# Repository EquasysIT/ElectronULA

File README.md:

# ElectronULA
Project to create replacement ULA board for the Acorn Electron. See Wiki

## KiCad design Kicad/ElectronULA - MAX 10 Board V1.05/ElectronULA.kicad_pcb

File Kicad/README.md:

The Core Carrier board is a board which requires the "EEpizza" board to be fitted. This is a board which actually contains the FPGA.
The MAX 10 Board is a complete board with everything required to replace the Acorn Electron ULA on a single board.

V1.05 is the latest board design including a Micro SD Card socket and enables the use of MMFS for people without the extra Plus 1 hardware.
Ensure the DIP switches are set correctly if connecting a Plus 1

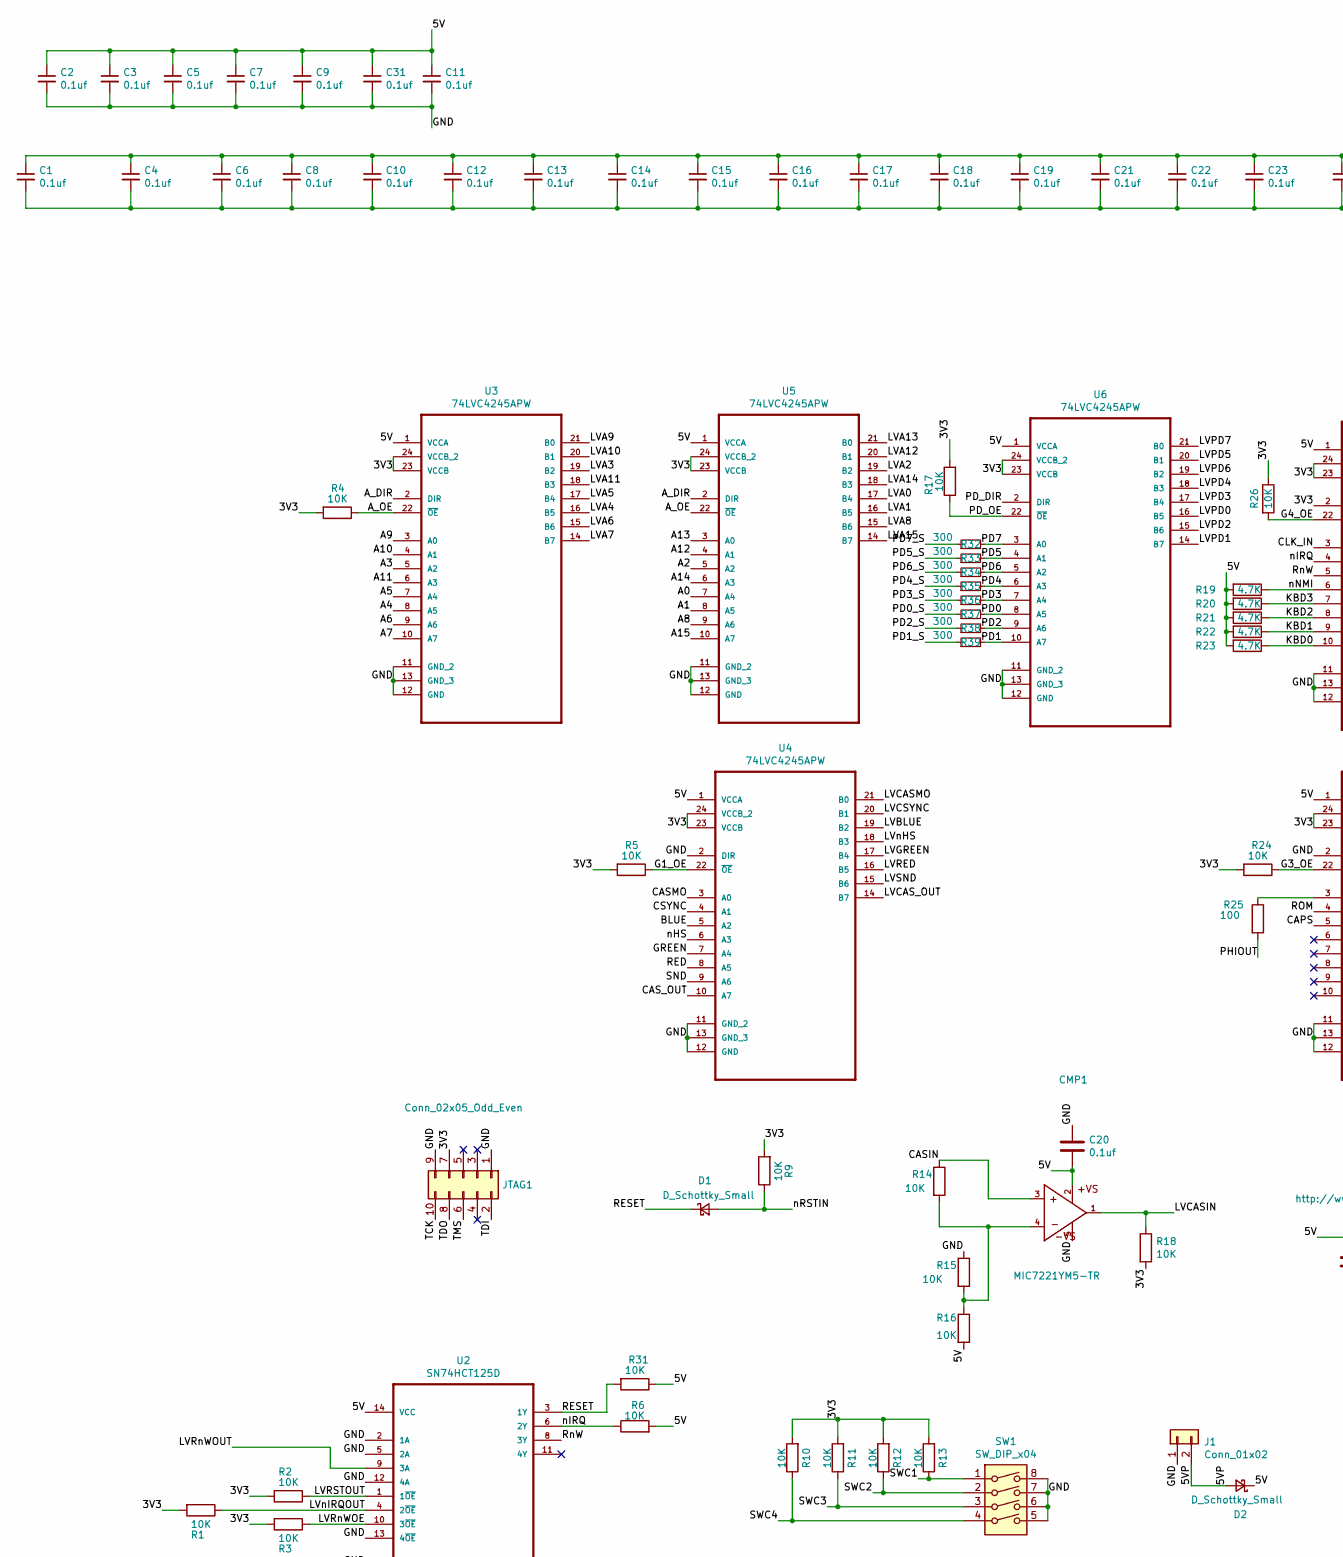
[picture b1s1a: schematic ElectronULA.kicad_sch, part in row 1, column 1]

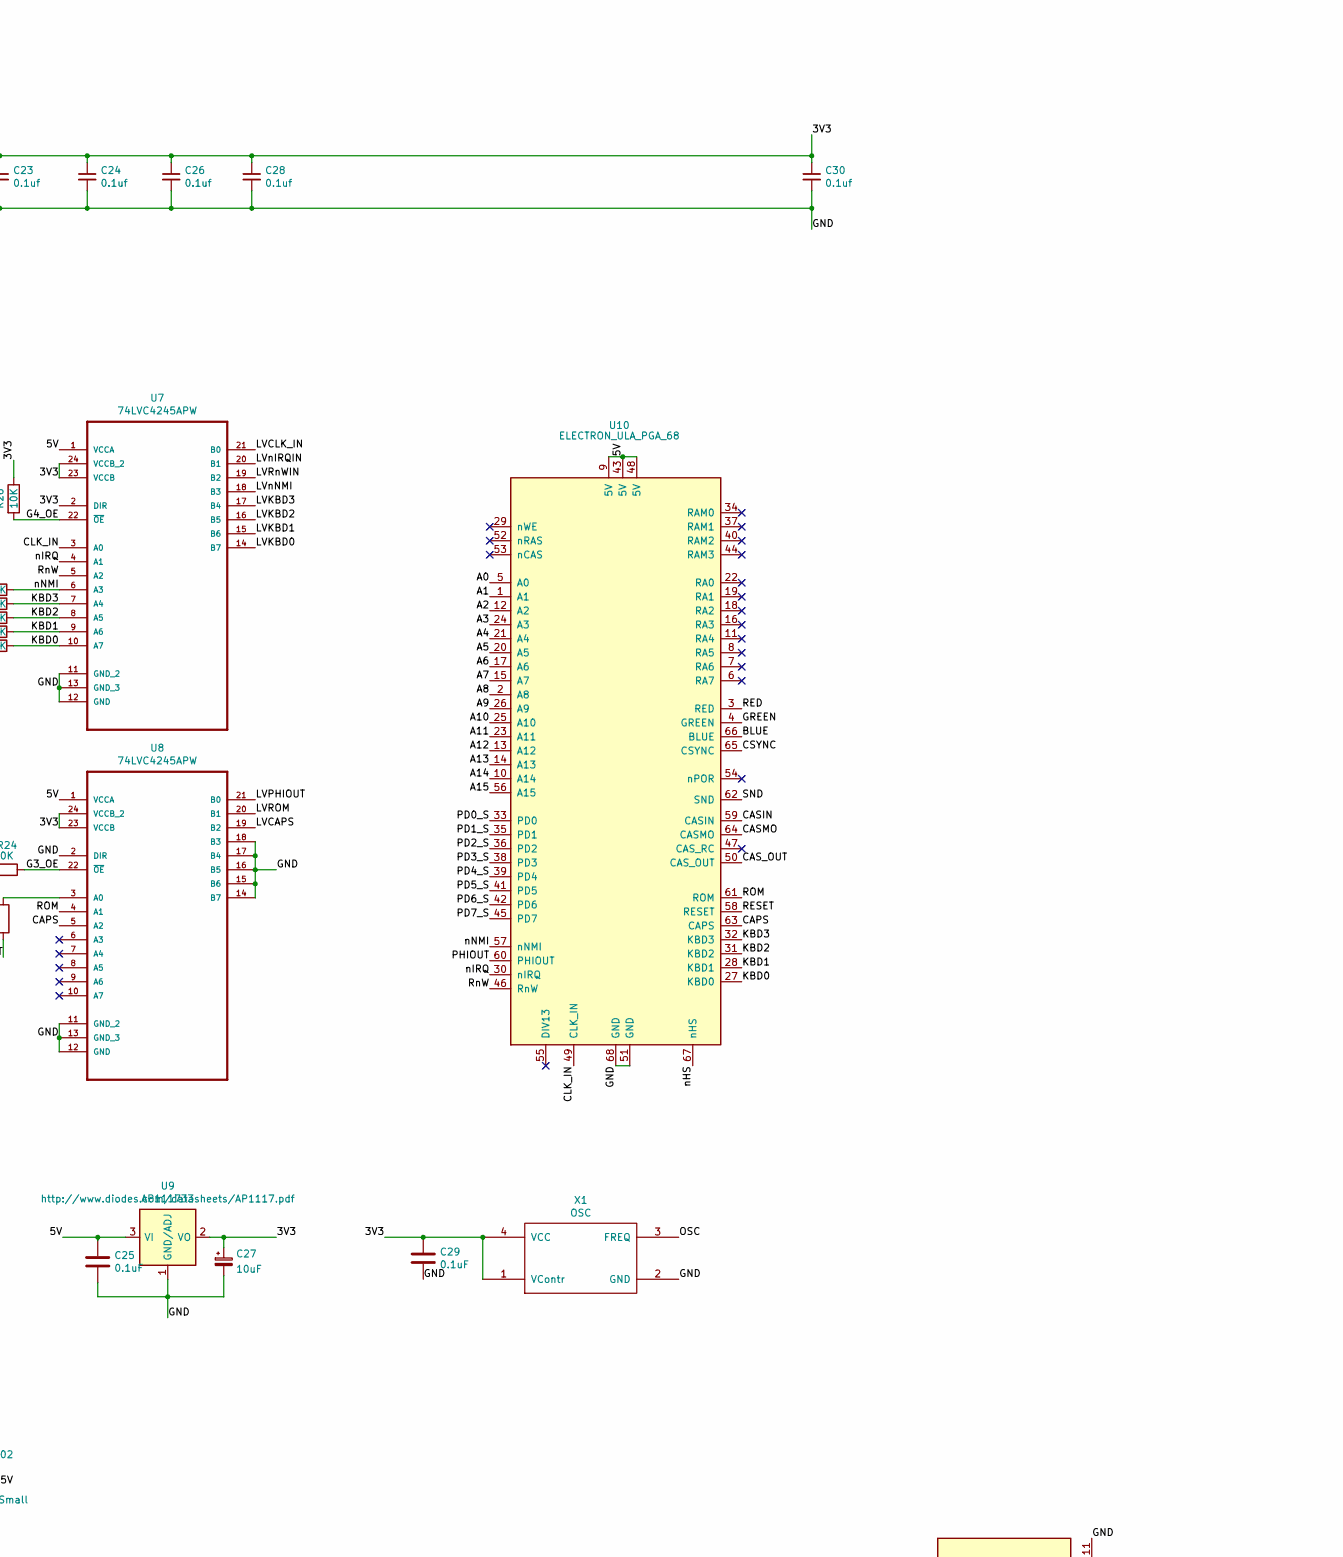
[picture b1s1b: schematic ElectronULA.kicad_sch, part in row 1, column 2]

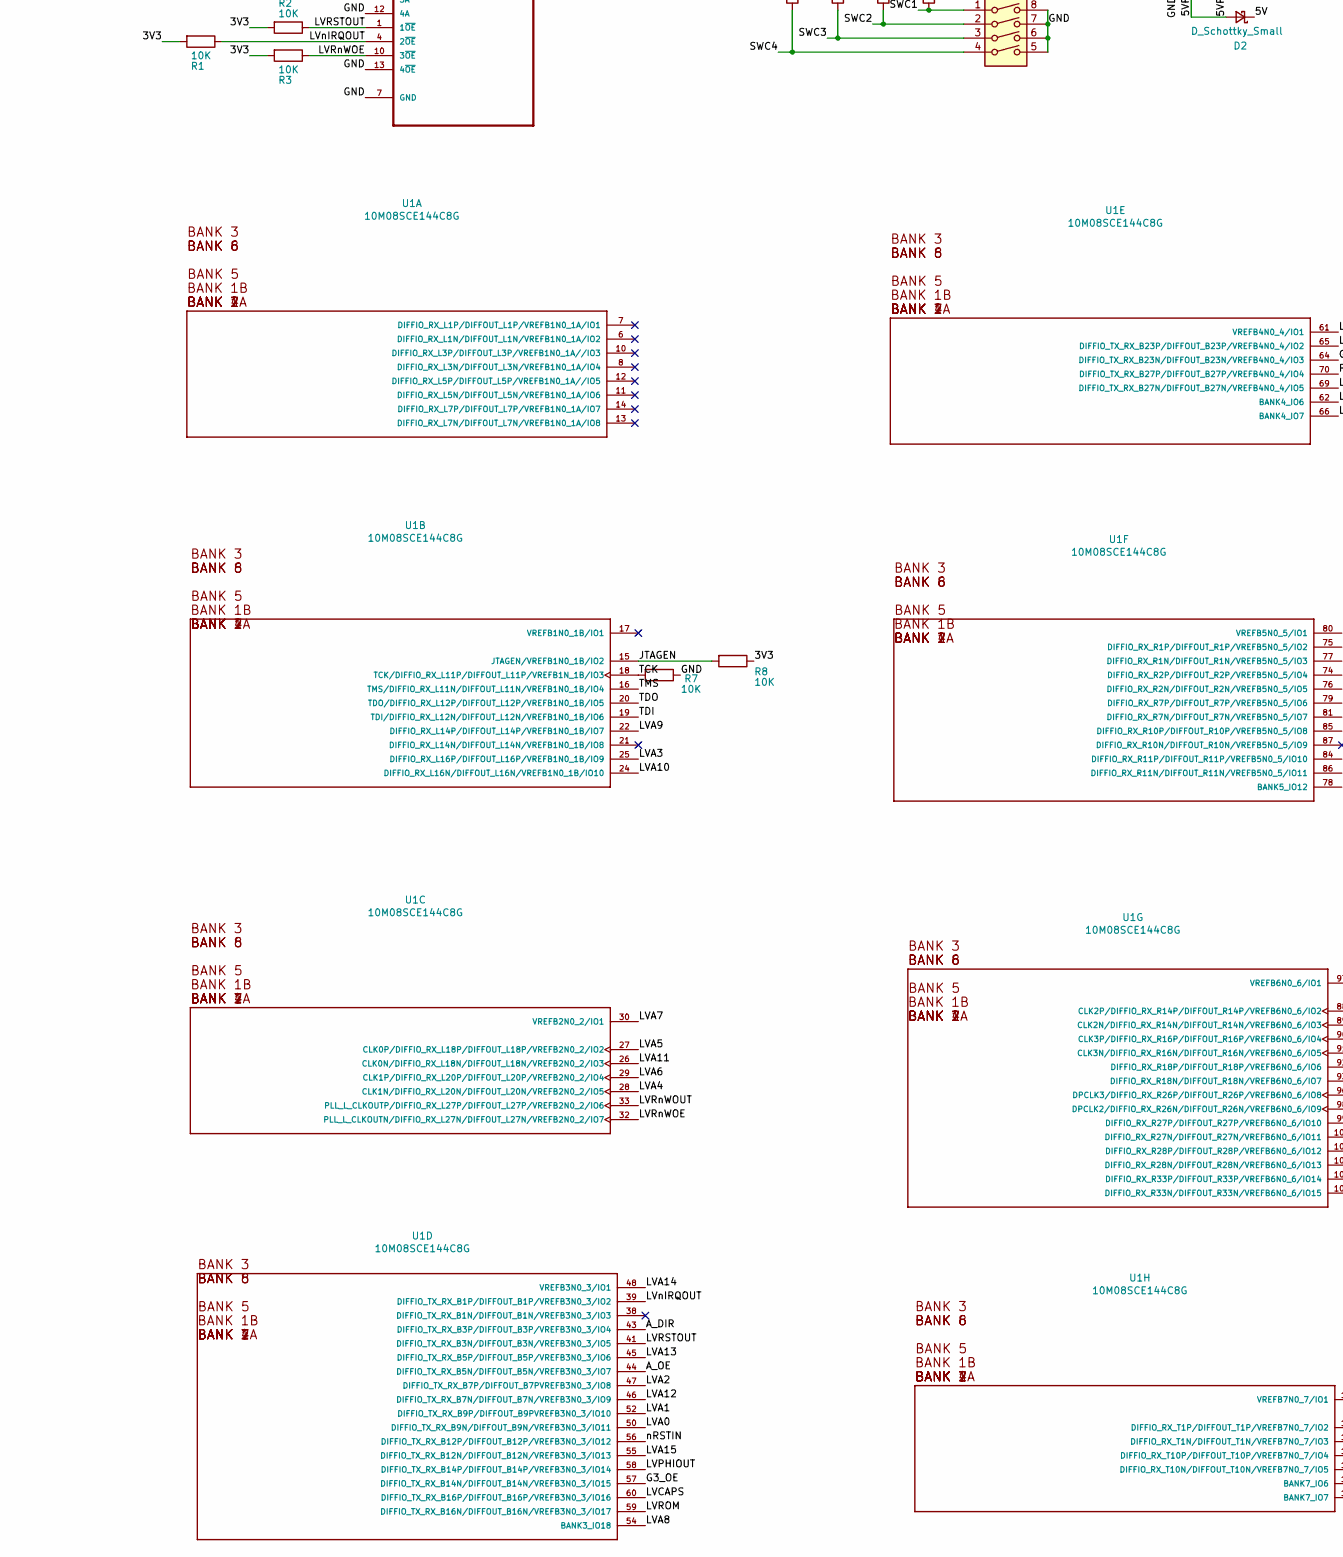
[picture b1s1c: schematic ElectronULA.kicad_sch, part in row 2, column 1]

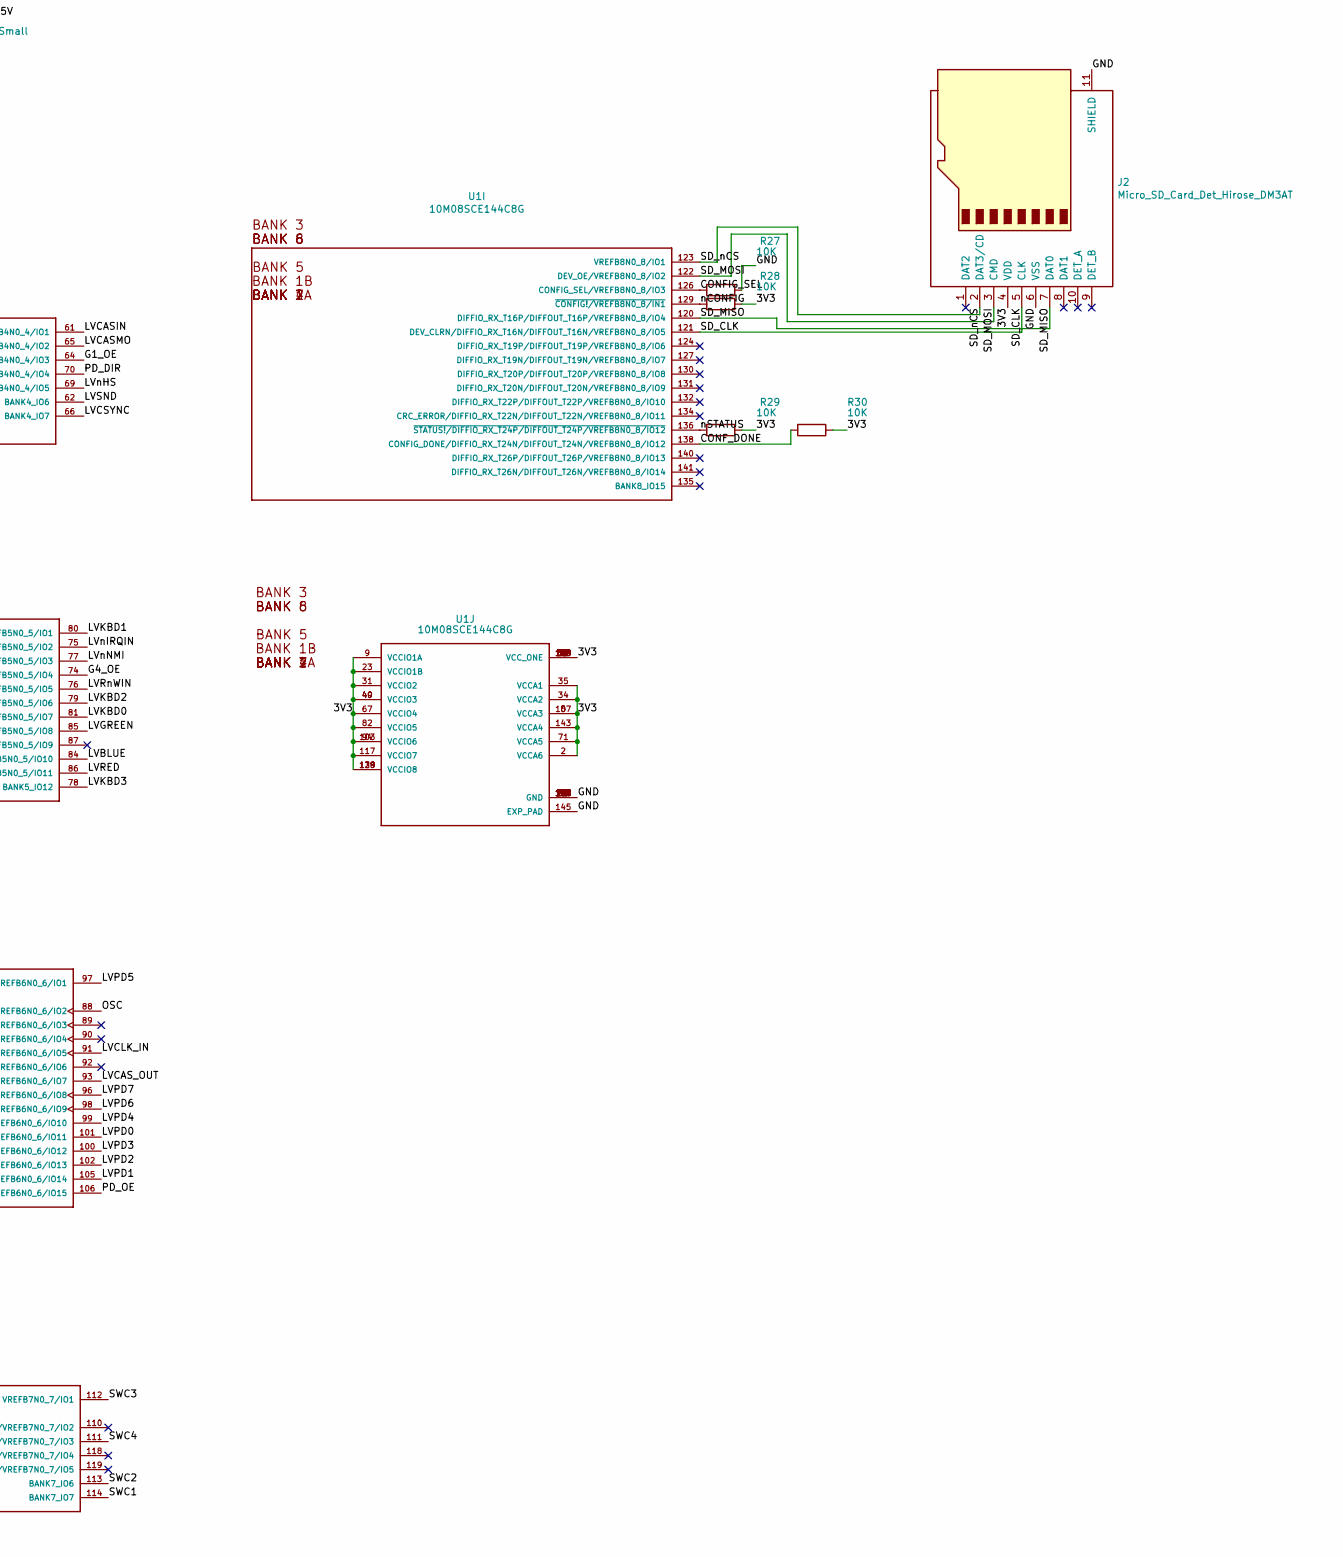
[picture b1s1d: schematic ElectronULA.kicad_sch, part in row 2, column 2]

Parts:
C1, C2, C3, C4, C5, C6, C7, C8, C9, C10, C11, C12, C13, C14, C15, C16, C17, C18, C19, C21, C22, C23, C24, C26, C28, C30, C31: 0.1uf; C_0603_1608Metric_Pad1.08x0.95mm_HandSolder
C20: 0.1uf; C_0805_2012Metric_Pad1.18x1.45mm_HandSolder
C25, C29: 0.1uF; C_0805_2012Metric_Pad1.18x1.45mm_HandSolder
C27: 10uF; C_0805_2012Metric_Pad1.18x1.45mm_HandSolder
CMP1: MIC7221YM5-TR; SOT-23-5
D1, D2: D_Schottky_Small; D_SOD-323_HandSoldering
J1: Conn_01x02; PinHeader_1x02_P2.54mm_Vertical
J2: Micro_SD_Card_Det_Hirose_DM3AT; microSD_HC_Hirose_DM3D-SF
JTAG1: Conn_02x05_Odd_Even; PinHeader_2x05_P2.54mm_Vertical
R1, R2, R3, R4, R5, R6, R7, R8, R10, R11, R12, R13, R17, R24, R26, R27, R28, R29, R30: 10K; R_0603_1608Metric_Pad0.98x0.95mm_HandSolder
R9, R14, R15, R16, R18, R31: 10K; R_0805_2012Metric_Pad1.20x1.40mm_HandSolder
R19: 4.7K; R_0805_2012Metric_Pad1.20x1.40mm_HandSolder
R20, R21, R22, R23: 4.7K; R_0603_1608Metric_Pad0.98x0.95mm_HandSolder
R25: 100; R_0805_2012Metric_Pad1.20x1.40mm_HandSolder
R32, R33, R34, R35, R36, R37, R38, R39: 300; R_0603_1608Metric_Pad0.98x0.95mm_HandSolder
SW1: SW_DIP_x04; SW_DIP_SPSTx04_Slide_Copal_CHS-04B_W7.62mm_P1.27mm
U1: 10M08SCE144C8G; QFP50P2200X2200X165-145N
U2: SN74HCT125D; TSSOP-14_4.4x5mm_P0.65mm
U3, U4, U5, U6, U7, U8: 74LVC4245APW; TSSOP-24_4.4x7.8mm_P0.65mm
U9: AP111733; SOT-223
U10: ELECTRON_ULA_PGA_68; PLCC-68_THT-Socket-Electron-ULA
X1: OSC; Crystal_SMD_7050_4Pads

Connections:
/3V3: C1.1, C4.1, C6.1, C8.1, C10.1, C12.1, C13.1, C14.1, C15.1, C16.1, C17.1, C18.1, C19.1, C21.1, C22.1, C23.1, C24.1, C26.1, C27.1, C28.1, C29.1, C30.1, J2.4 (VDD), JTAG1.7, R1.2, R2.2, R3.2, R4.2, R5.2, R8.1, R9.2, R10.2, R11.2, R12.2, R13.2, R17.2, R18.2, R24.2, R26.1, R28.1, R29.1, R30.1, U1.1 (VCC_ONE), U1.2 (VCCA6), U1.5 (VCCA3), U1.9 (VCCIO1A), U1.23 (VCCIO1B), U1.31 (VCCIO2), U1.34 (VCCA2), U1.35 (VCCA1), U1.36 (VCC_ONE), U1.37 (VCC_ONE), U1.40 (VCCIO3), U1.49 (VCCIO3), U1.51 (VCC_ONE), U1.67 (VCCIO4), U1.71 (VCCA5), U1.72 (VCC_ONE), U1.73 (VCC_ONE), U1.82 (VCCIO5), U1.94 (VCCIO6), U1.103 (VCCIO6), U1.107 (VCCA3), U1.108 (VCC_ONE), U1.109 (VCC_ONE), U1.115 (VCC_ONE), U1.117 (VCCIO7), U1.128 (VCCIO8), U1.139 (VCCIO8), U1.143 (VCCA4), U1.144 (VCC_ONE), U3.23 (VCCB), U3.24 (VCCB_2), U4.23 (VCCB), U4.24 (VCCB_2), U5.23 (VCCB), U5.24 (VCCB_2), U6.23 (VCCB), U6.24 (VCCB_2), U7.2 (DIR), U7.23 (VCCB), U7.24 (VCCB_2), U8.23 (VCCB), U8.24 (VCCB_2), U9.2 (VO), X1.1 (VContr), X1.4 (VCC)
/5V: C2.1, C3.1, C5.1, C7.1, C9.1, C11.1, C20.2, C25.1, C31.1, CMP1.2 (+VS), D2.1 (K), R6.2, R16.2, R19.2, R20.2, R21.2, R22.2, R23.2, R31.1, U2.14 (VCC), U3.1 (VCCA), U4.1 (VCCA), U5.1 (VCCA), U6.1 (VCCA), U7.1 (VCCA), U8.1 (VCCA), U9.3 (VI), U10.9 (5V), U10.43 (5V), U10.48 (5V)
/5VP: D2.2 (A), J1.2
/A0: U5.7 (A4), U10.5 (A0)
/A1: U5.8 (A5), U10.1 (A1)
/A2: U5.5 (A2), U10.12 (A2)
/A3: U3.5 (A2), U10.24 (A3)
/A4: U3.8 (A5), U10.21 (A4)
/A5: U3.7 (A4), U10.20 (A5)
/A6: U3.9 (A6), U10.17 (A6)
/A7: U3.10 (A7), U10.15 (A7)
/A8: U5.9 (A6), U10.2 (A8)
/A9: U3.3 (A0), U10.26 (A9)
/A10: U3.4 (A1), U10.25 (A10)
/A11: U3.6 (A3), U10.23 (A11)
/A12: U5.4 (A1), U10.13 (A12)
/A13: U5.3 (A0), U10.14 (A13)
/A14: U5.6 (A3), U10.10 (A14)
/A15: U5.10 (A7), U10.56 (A15)
/A_DIR: U1.43 (DIFFIO_TX_RX_B3P/DIFFOUT_B3P/VREFB3N0_3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), U3.2 (DIR), U5.2 (DIR)
/A_OE: R4.1, U1.44 (DIFFIO_TX_RX_B5N/DIFFOUT_B5N/VREFB3N0_3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), U3.22 (~OE), U5.22 (~OE)
/BLUE: U4.5 (A2), U10.66 (BLUE)
/CAPS: U8.5 (A2), U10.63 (CAPS)
/CASIN: CMP1.3 (IN+), R14.1, U10.59 (CASIN)
/CASMO: U4.3 (A0), U10.64 (CASMO)
/CAS_OUT: U4.10 (A7), U10.50 (CAS_OUT)
/CLK_IN: U7.3 (A0), U10.49 (CLK_IN)
/CONFIG_SEL: R27.2, U1.126 (CONFIG_SEL/VREFB8N0_8/IO3)
/CONF_DONE: R30.2, U1.138 (CONFIG_DONE/DIFFIO_RX_T24N/DIFFOUT_T24N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)
/CSYNC: U4.4 (A1), U10.65 (CSYNC)
/G1_OE: R5.1, U1.64 (DIFFIO_TX_RX_B23N/DIFFOUT_B23N/VREFB4N0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), U4.22 (~OE)
/G3_OE: R24.1, U1.57 (DIFFIO_TX_RX_B14N/DIFFOUT_B14N/VREFB3N0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), U8.22 (~OE)
/G4_OE: R26.2, U1.74 (DIFFIO_RX_R2P/DIFFOUT_R2P/VREFB5N0_5/IO4), U7.22 (~OE)
/GND: C1.2, C2.2, C3.2, C4.2, C5.2, C6.2, C7.2, C8.2, C9.2, C10.2, C11.2, C12.2, C13.2, C14.2, C15.2, C16.2, C17.2, C18.2, C19.2, C20.1, C21.2, C22.2, C23.2, C24.2, C25.2, C26.2, C27.2, C28.2, C29.2, C30.2, C31.2, CMP1.5 (-VS), J1.1, J2.6 (VSS), J2.11 (SHIELD), JTAG1.1, JTAG1.9, R7.1, R15.1, R27.1, SW1.5, SW1.6, SW1.7, SW1.8, U1.3 (GND), U1.4 (GND), U1.42 (GND), U1.53 (GND), U1.63 (GND), U1.68 (GND), U1.83 (GND), U1.95 (GND), U1.104 (GND), U1.116 (GND), U1.125 (GND), U1.133 (GND), U1.137 (GND), U1.142 (GND), U1.145 (EXP_PAD), U2.2 (1A), U2.5 (2A), U2.7 (GND), U2.12 (4A), U2.13 (4~OE), U3.11 (GND_2), U3.12 (GND), U3.13 (GND_3), U4.2 (DIR), U4.11 (GND_2), U4.12 (GND), U4.13 (GND_3), U5.11 (GND_2), U5.12 (GND), U5.13 (GND_3), U6.11 (GND_2), U6.12 (GND), U6.13 (GND_3), U7.11 (GND_2), U7.12 (GND), U7.13 (GND_3), U8.2 (DIR), U8.11 (GND_2), U8.12 (GND), U8.13 (GND_3), U8.14 (B7), U8.15 (B6), U8.16 (B5), U8.17 (B4), U8.18 (B3), U9.1 (GND/ADJ), U10.51 (GND), U10.68 (GND), X1.2 (GND); also elsewhere on the board
/GREEN: U4.7 (A4), U10.4 (GREEN)
/JTAGEN: R8.2, U1.15 (JTAGEN/VREFB1N0_1B/IO2)
/KBD0: R23.1, U7.10 (A7), U10.27 (KBD0)
/KBD1: R22.1, U7.9 (A6), U10.28 (KBD1)
/KBD2: R21.1, U7.8 (A5), U10.31 (KBD2)
/KBD3: R20.1, U7.7 (A4), U10.32 (KBD3)
/LVA0: U1.50 (DIFFIO_TX_RX_B9N/DIFFOUT_B9N/VREFB3N0_3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), U5.17 (B4)
/LVA1: U1.52 (DIFFIO_TX_RX_B9P/DIFFOUT_B9PVREFB3N0_3/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), U5.16 (B5)
/LVA2: U1.47 (DIFFIO_TX_RX_B7P/DIFFOUT_B7PVREFB3N0_3/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), U5.19 (B2)
/LVA3: U1.25 (DIFFIO_RX_L16P/DIFFOUT_L16P/VREFB1N0_1B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), U3.19 (B2)
/LVA4: U1.28 (CLK1N/DIFFIO_RX_L20N/DIFFOUT_L20N/VREFB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), U3.16 (B5)
/LVA5: U1.27 (CLK0P/DIFFIO_RX_L18P/DIFFOUT_L18P/VREFB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), U3.17 (B4)
/LVA6: U1.29 (CLK1P/DIFFIO_RX_L20P/DIFFOUT_L20P/VREFB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), U3.15 (B6)
/LVA7: U1.30 (VREFB2N0_2/IO1), U3.14 (B7)
/LVA8: U1.54 (BANK3_IO18), U5.15 (B6)
/LVA9: U1.22 (DIFFIO_RX_L14P/DIFFOUT_L14P/VREFB1N0_1B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), U3.21 (B0)
/LVA10: U1.24 (DIFFIO_RX_L16N/DIFFOUT_L16N/VREFB1N0_1B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), U3.20 (B1)
/LVA11: U1.26 (CLK0N/DIFFIO_RX_L18N/DIFFOUT_L18N/VREFB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), U3.18 (B3)
/LVA12: U1.46 (DIFFIO_TX_RX_B7N/DIFFOUT_B7N/VREFB3N0_3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), U5.20 (B1)
/LVA13: U1.45 (DIFFIO_TX_RX_B5P/DIFFOUT_B5P/VREFB3N0_3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), U5.21 (B0)
/LVA14: U1.48 (VREFB3N0_3/IO1), U5.18 (B3)
/LVA15: U1.55 (DIFFIO_TX_RX_B12N/DIFFOUT_B12N/VREFB3N0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), U5.14 (B7)
/LVBLUE: U1.84 (DIFFIO_RX_R11P/DIFFOUT_R11P/VREFB5N0_5/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), U4.19 (B2)
/LVCAPS: U1.60 (DIFFIO_TX_RX_B16P/DIFFOUT_B16P/VREFB3N0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), U8.19 (B2)
/LVCASIN: CMP1.1 (OUT), R18.1, U1.61 (VREFB4N0_4/IO1)
/LVCASMO: U1.65 (DIFFIO_TX_RX_B23P/DIFFOUT_B23P/VREFB4N0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), U4.21 (B0)
/LVCAS_OUT: U1.93 (DIFFIO_RX_R18N/DIFFOUT_R18N/VREFB6N0_6/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), U4.14 (B7)
/LVCLK_IN: U1.91 (CLK3N/DIFFIO_RX_R16N/DIFFOUT_R16N/VREFB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), U7.21 (B0)
/LVCSYNC: U1.66 (BANK4_IO7), U4.20 (B1)
/LVGREEN: U1.85 (DIFFIO_RX_R10P/DIFFOUT_R10P/VREFB5N0_5/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), U4.17 (B4)
/LVKBD0: U1.81 (DIFFIO_RX_R7N/DIFFOUT_R7N/VREFB5N0_5/IO7), U7.14 (B7)
/LVKBD1: U1.80 (VREFB5N0_5/IO1), U7.15 (B6)
/LVKBD2: U1.79 (DIFFIO_RX_R7P/DIFFOUT_R7P/VREFB5N0_5/IO6), U7.16 (B5)
/LVKBD3: U1.78 (BANK5_IO12), U7.17 (B4)
/LVPD0: U1.101 (DIFFIO_RX_R27N/DIFFOUT_R27N/VREFB6N0_6/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), U6.16 (B5)
/LVPD1: U1.105 (DIFFIO_RX_R33P/DIFFOUT_R33P/VREFB6N0_6/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), U6.14 (B7)
/LVPD2: U1.102 (DIFFIO_RX_R28N/DIFFOUT_R28N/VREFB6N0_6/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), U6.15 (B6)
/LVPD3: U1.100 (DIFFIO_RX_R28P/DIFFOUT_R28P/VREFB6N0_6/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), U6.17 (B4)
/LVPD4: U1.99 (DIFFIO_RX_R27P/DIFFOUT_R27P/VREFB6N0_6/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), U6.18 (B3)
/LVPD5: U1.97 (VREFB6N0_6/IO1), U6.20 (B1)
/LVPD6: U1.98 (DPCLK2/DIFFIO_RX_R26N/DIFFOUT_R26N/VREF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), U6.19 (B2)
/LVPD7: U1.96 (DPCLK3/DIFFIO_RX_R26P/DIFFOUT_R26P/VREF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), U6.21 (B0)
/LVPHIOUT: U1.58 (DIFFIO_TX_RX_B14P/DIFFOUT_B14P/VREFB3N0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), U8.21 (B0)
/LVRED: U1.86 (DIFFIO_RX_R11N/DIFFOUT_R11N/VREFB5N0_5/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), U4.16 (B5)
/LVROM: U1.59 (DIFFIO_TX_RX_B16N/DIFFOUT_B16N/VREFB3N0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), U8.20 (B1)
/LVRSTOUT: R2.1, U1.41 (DIFFIO_TX_RX_B3N/DIFFOUT_B3N/VREFB3N0_3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), U2.1 (1~OE)
/LVRnWIN: U1.76 (DIFFIO_RX_R2N/DIFFOUT_R2N/VREFB5N0_5/IO5), U7.19 (B2)
/LVRnWOE: R3.1, U1.32 (PLL_L_CLKOUTN/DIFFIO_RX_L27N/DIFFOUT_L2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), U2.10 (3~OE)
/LVRnWOUT: U1.33 (PLL_L_CLKOUTP/DIFFIO_RX_L27P/DIFFOUT_L2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), U2.9 (3A)
/LVSND: U1.62 (BANK4_IO6), U4.15 (B6)
/LVnHS: U1.69 (DIFFIO_TX_RX_B27N/DIFFOUT_B27N/VREFB4N0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), U4.18 (B3)
/LVnIRQIN: U1.75 (DIFFIO_RX_R1P/DIFFOUT_R1P/VREFB5N0_5/IO2), U7.20 (B1)
/LVnIRQOUT: R1.1, U1.39 (DIFFIO_TX_RX_B1P/DIFFOUT_B1P/VREFB3N0_3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), U2.4 (2~OE)
/LVnNMI: U1.77 (DIFFIO_RX_R1N/DIFFOUT_R1N/VREFB5N0_5/IO3), U7.18 (B3)
/OSC: U1.88 (CLK2P/DIFFIO_RX_R14P/DIFFOUT_R14P/VREFB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), X1.3 (FREQ)
/PD0: R37.2, U6.8 (A5)
/PD0_S: R37.1, U10.33 (PD0)
/PD1: R39.2, U6.10 (A7)
/PD1_S: R39.1, U10.35 (PD1)
/PD2: R38.2, U6.9 (A6)
/PD2_S: R38.1, U10.36 (PD2)
/PD3: R36.2, U6.7 (A4)
/PD3_S: R36.1, U10.38 (PD3)
/PD4: R35.2, U6.6 (A3)
/PD4_S: R35.1, U10.39 (PD4)
/PD5: R33.2, U6.4 (A1)
/PD5_S: R33.1, U10.41 (PD5)
/PD6: R34.2, U6.5 (A2)
/PD6_S: R34.1, U10.42 (PD6)
/PD7: R32.2, U6.3 (A0)
/PD7_S: R32.1, U10.45 (PD7)
/PD_DIR: U1.70 (DIFFIO_TX_RX_B27P/DIFFOUT_B27P/VREFB4N0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), U6.2 (DIR)
/PD_OE: R17.1, U1.106 (DIFFIO_RX_R33N/DIFFOUT_R33N/VREFB6N0_6/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), U6.22 (~OE)
/PHIOUT: R25.2, U10.60 (PHIOUT)
/RED: U4.8 (A5), U10.3 (RED)
/RESET: D1.1 (K), R31.2, U2.3 (1Y), U10.58 (RESET)
/ROM: U8.4 (A1), U10.61 (ROM)
/RnW: U2.8 (3Y), U7.5 (A2), U10.46 (RnW)
/SD_CLK: J2.5 (CLK), U1.121 (DEV_CLRN/DIFFIO_RX_T16N/DIFFOUT_T16N/VR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)
/SD_MISO: J2.7 (DAT0), U1.120 (DIFFIO_RX_T16P/DIFFOUT_T16P/VREFB8N0_8/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)
/SD_MOSI: J2.3 (CMD), U1.122 (DEV_OE/VREFB8N0_8/IO2)
/SD_nCS: J2.2 (DAT3/CD), U1.123 (VREFB8N0_8/IO1)
/SND: U4.9 (A6), U10.62 (SND)
/SWC1: R13.1, SW1.1, U1.114 (BANK7_IO7)
/SWC2: R12.1, SW1.2, U1.113 (BANK7_IO6)
/SWC3: R11.1, SW1.3, U1.112 (VREFB7N0_7/IO1)
/SWC4: R10.1, SW1.4, U1.111 (DIFFIO_RX_T1N/DIFFOUT_T1N/VREFB7N0_7/IO3)
/TCK: JTAG1.10, R7.2, U1.18 (TCK/DIFFIO_RX_L11P/DIFFOUT_L11P/VREFB1N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)
/TDI: JTAG1.2, U1.19 (TDI/DIFFIO_RX_L12N/DIFFOUT_L12N/VREFB1N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)
/TDO: JTAG1.8, U1.20 (TDO/DIFFIO_RX_L12P/DIFFOUT_L12P/VREFB1N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)
/TMS: JTAG1.6, U1.16 (TMS/DIFFIO_RX_L11N/DIFFOUT_L11N/VREFB1N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)
/nCONFIG: R28.2, U1.129 (~CONFIG!/VREFB8N0_8/IN1)
/nHS: U4.6 (A3), U10.67 (nHS)
/nIRQ: R6.1, U2.6 (2Y), U7.4 (A1), U10.30 (nIRQ)
/nNMI: R19.1, U7.6 (A3), U10.57 (nNMI)
/nRSTIN: D1.2 (A), R9.1, U1.56 (DIFFIO_TX_RX_B12P/DIFFOUT_B12P/VREFB3N0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)
/nSTATUS: R29.2, U1.136 (~STATUS!/DIFFIO_RX_T24P/DIFFOUT_T24P/VR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)
unnamed: CMP1.4 (IN-), R14.2, R15.2, R16.1
unnamed: R25.1, U8.3 (A0)

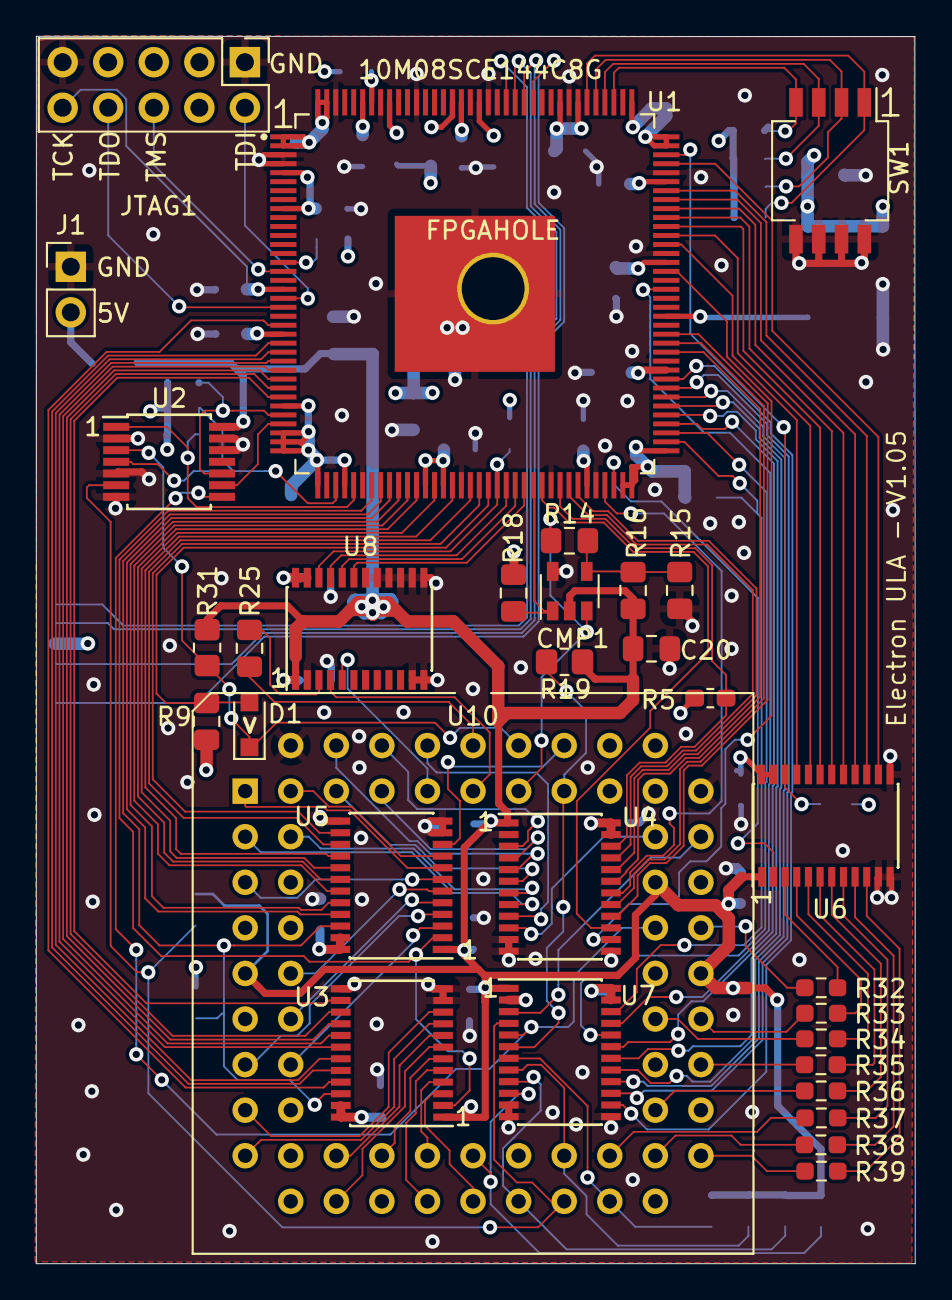
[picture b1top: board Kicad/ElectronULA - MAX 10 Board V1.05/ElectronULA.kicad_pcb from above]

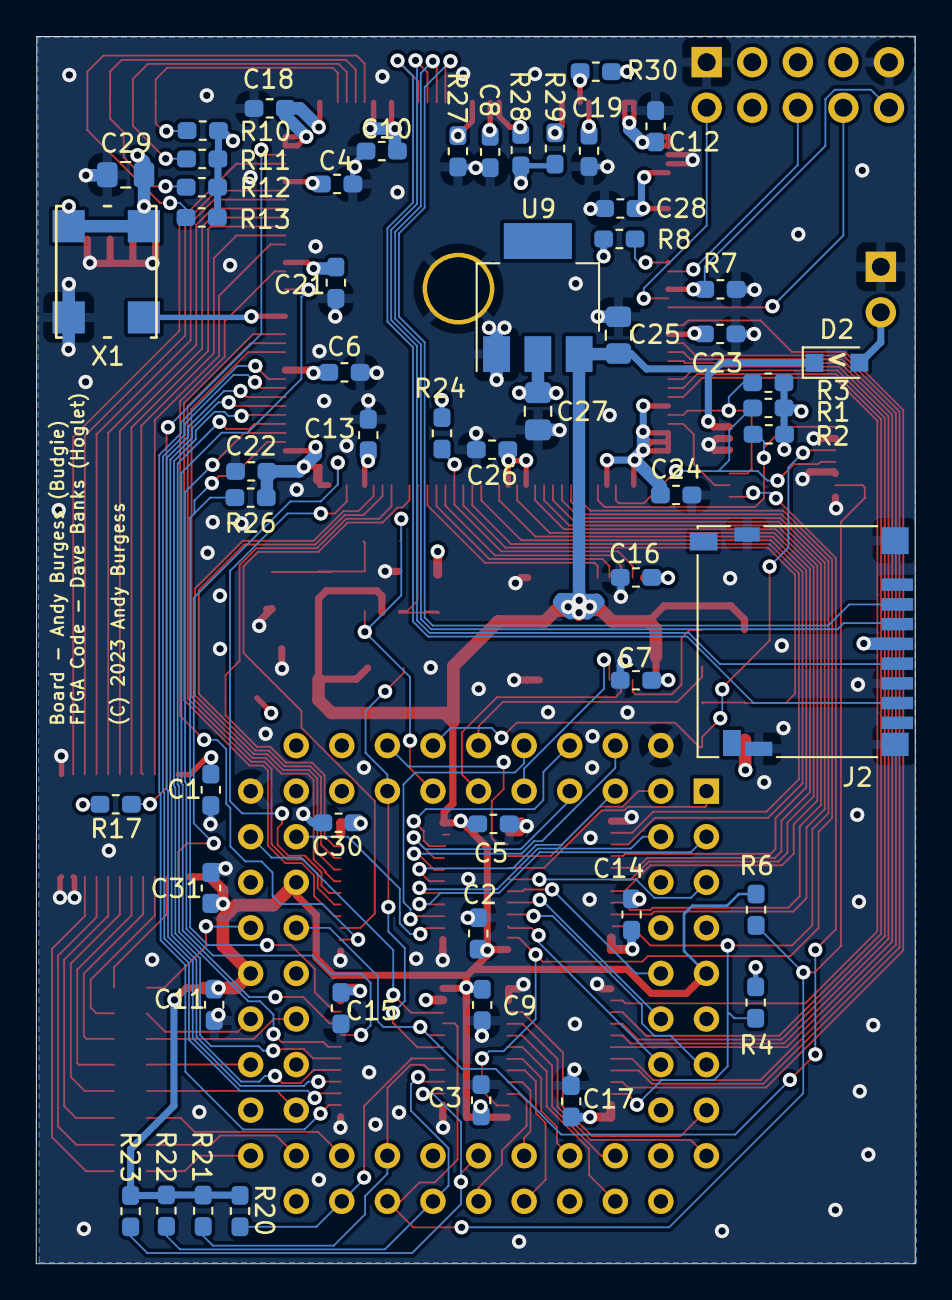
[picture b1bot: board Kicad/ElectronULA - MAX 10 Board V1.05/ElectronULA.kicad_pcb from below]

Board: 4 copper layers, 49.0 x 68.4 mm, 89 parts (56 on the bottom side), 133 nets.

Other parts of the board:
FPGAHOLE: MountingHole_2.7mm_M2.5_ISO7380_Pad

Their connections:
/GND: FPGAHOLE.1; also elsewhere on the board

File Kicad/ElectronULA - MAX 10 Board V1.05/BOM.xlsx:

Acorn Electron ULA - MAX 10 Board - V1.05
Bill of Materials
Note: This board can only be fitted to a PGA68 socket on the Electron board. Th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
Tips
1. Fit the ULA socket pins last (17)
2. Soldering the MAX 10 FPGA - Place some solder paste on the large central pad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
3. I recommend using a gel like flux for the SMD chips. Run plenty along each r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
4. All the passives (capacitors, resistors), comparator and regulator etc are b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
Excellent drag soldering guide here "https://www.youtube.com/watch?v=nyele3CIs-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
Id | Designator | Package | Quantity | Designation | Description | Supplier and ref
1 | R20, R21, R22, R23 | R_0603_1608Metric_Pad1.05x0.95mm_HandSolder | 4 | 4.7K Resistor | Pullups for Keyboard input
2 | D1,D2 | D_SOD-323_HandSoldering | 2 | Schottky Diode | BAT54 | https://www.digikey.co.uk/product-detail/en/on-semiconductor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
3 | U2 | TSSOP-14_4.4x5mm_P0.65mm | 1 | 74HCT125D | Quad Buffer | https://www.digikey.co.uk/product-detail/en/nexperia-usa-inc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,118/172…
4 | R1, R2, R3, R4, R5, R6, R7, R8, R10, R11, R12, R13, R17, R24, R26, R27, R28, R2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 | R_0603_1608Metric_Pad1.05x0.95mm_HandSolder | 19 | 10K Resistor
5 | SW1 | SW_DIP_SPSTx04_Slide_Copal_CHS-04B_W7.62mm_P1.27mm | 1 | SW_DIP_x04 | Configuration Switch | https://www.digikey.co.uk/product-detail/en/nidec-copal-elec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
6 | J1 | PinHeader_1x02_P2.54mm_Vertical | 1 | Conn_01x02 | 5V Power Input Normal Square Pins
7 | JTAG1 | PinHeader_2x05_P2.54mm_Vertical | 1 | Conn_02x05_Odd_Even | JTAG Pins Normal Square Pins
8 | C1, C2, C3, C4, C5, C6, C7, C8, C9, C10, C11, C12, C13, C14, C15, C16, C17, C18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 | C_0603_1608Metric_Pad1.05x0.95mm_HandSolder | 26 | 0.1uf Capacitor
9 | X1 | Crystal_SMD_7050_4Pads | 1 | Oscillator | 16Mhz Oscillator | Not required unless Electron 16Mhz signal is very poor. FPGA will require an up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
10 | C27 | C_0805_2012Metric_Pad1.15x1.40mm_HandSolder | 1 | 10uF Capacitor Tantalum
11 | U9 | SOT-223 | 1 | AP2114H-3.3TRG1 | Regulator | https://www.digikey.co.uk/product-detail/en/diodes-incorpora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
12 | C20,C25,C29 | C_0805_2012Metric_Pad1.15x1.40mm_HandSolder | 3 | 0.1uf Capacitor
13 | R9, R14, R15, R16, R18, R31 | R_0805_2012Metric_Pad1.15x1.40mm_HandSolder | 5 | 10K Resistor
14 | R19 | R_0805_2012Metric_Pad1.15x1.40mm_HandSolder | 1 | 4.7K Resistor | nNMI 5V Pullup
15 | U1 | EQFP | 1 | 10M08SCE144C8G | Intel MAX 10 FPGA | https://www.digikey.co.uk/products/en?keywords=10M08SCE144C8G
16 | U3, U4, U5, U6, U7, U8 | TSSOP-24_4.4x7.8mm_P0.65mm | 6 | 74LVC4245APW | Octal Transceiver | https://www.digikey.co.uk/product-detail/en/nexperia-usa-inc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
17 | U10 | ULA Socket Pins - 1x40 - 2.54mm Pin Headers | 2 | PGA 68 Pin Layout | ULA Socket Pins Turned Pin Type | https://hobbycomponents.com/connectors/439-01-254mm-40way-si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
18 | CMP1 | SOT-23-5 | 1 | MIC7221YM5-TR | Comparator | https://www.digikey.co.uk/product-detail/en/microchip-techno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
19 | R25 | R_0805_2012Metric_Pad1.15x1.40mm_HandSolder | 1 | 100R Resistor | CPU Clock Noise Reducer
20 | J2 | Hirose 8 Way Right Angle Micro SD Memory Card Connector | 1 | Micro SD Card Holder | SD Card Holder | https://uk.rs-online.com/web/p/memory-card-connectors/7388809
21 | Turned pin socket headers to make ULA socket for Electron circuit board | ULA Socket for Electron circuit board | 1 |  | Pack of 5 x 40 pin | https://hobbycomponents.com/connectors/392-01-254mm-40way-si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
22 | R32, R33, R34, R35, R36, R37, R38, R39 | R_0603_1608Metric_Pad1.05x0.95mm_HandSolder | 8 | 33 Ohm Resistor | Slow down Data Buffers to reduce noise

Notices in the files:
VHDL/MAX 10 Board V1.02/ElectronULA.qsf:
Copyright (C) 2017  Intel Corporation. All rights reserved.
Kicad/ElectronULA - MAX 10 Board V1.03/ElectronULA.kicad_pcb:
(C) 2020 Andy Burgess
Kicad/ElectronULA - MAX 10 Board V1.05/ElectronULA.kicad_pcb:
(C) 2023 Andy Burgess
